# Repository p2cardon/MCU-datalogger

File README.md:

# MCU-datalogger
Example Kicad 6, Projects, Tips, and Recipes book
This repository has been created to learn basic functions of GIT usage, to synchronise KiCad projects
It's subject to be removed at any time without any warning
Don't rely on it's content

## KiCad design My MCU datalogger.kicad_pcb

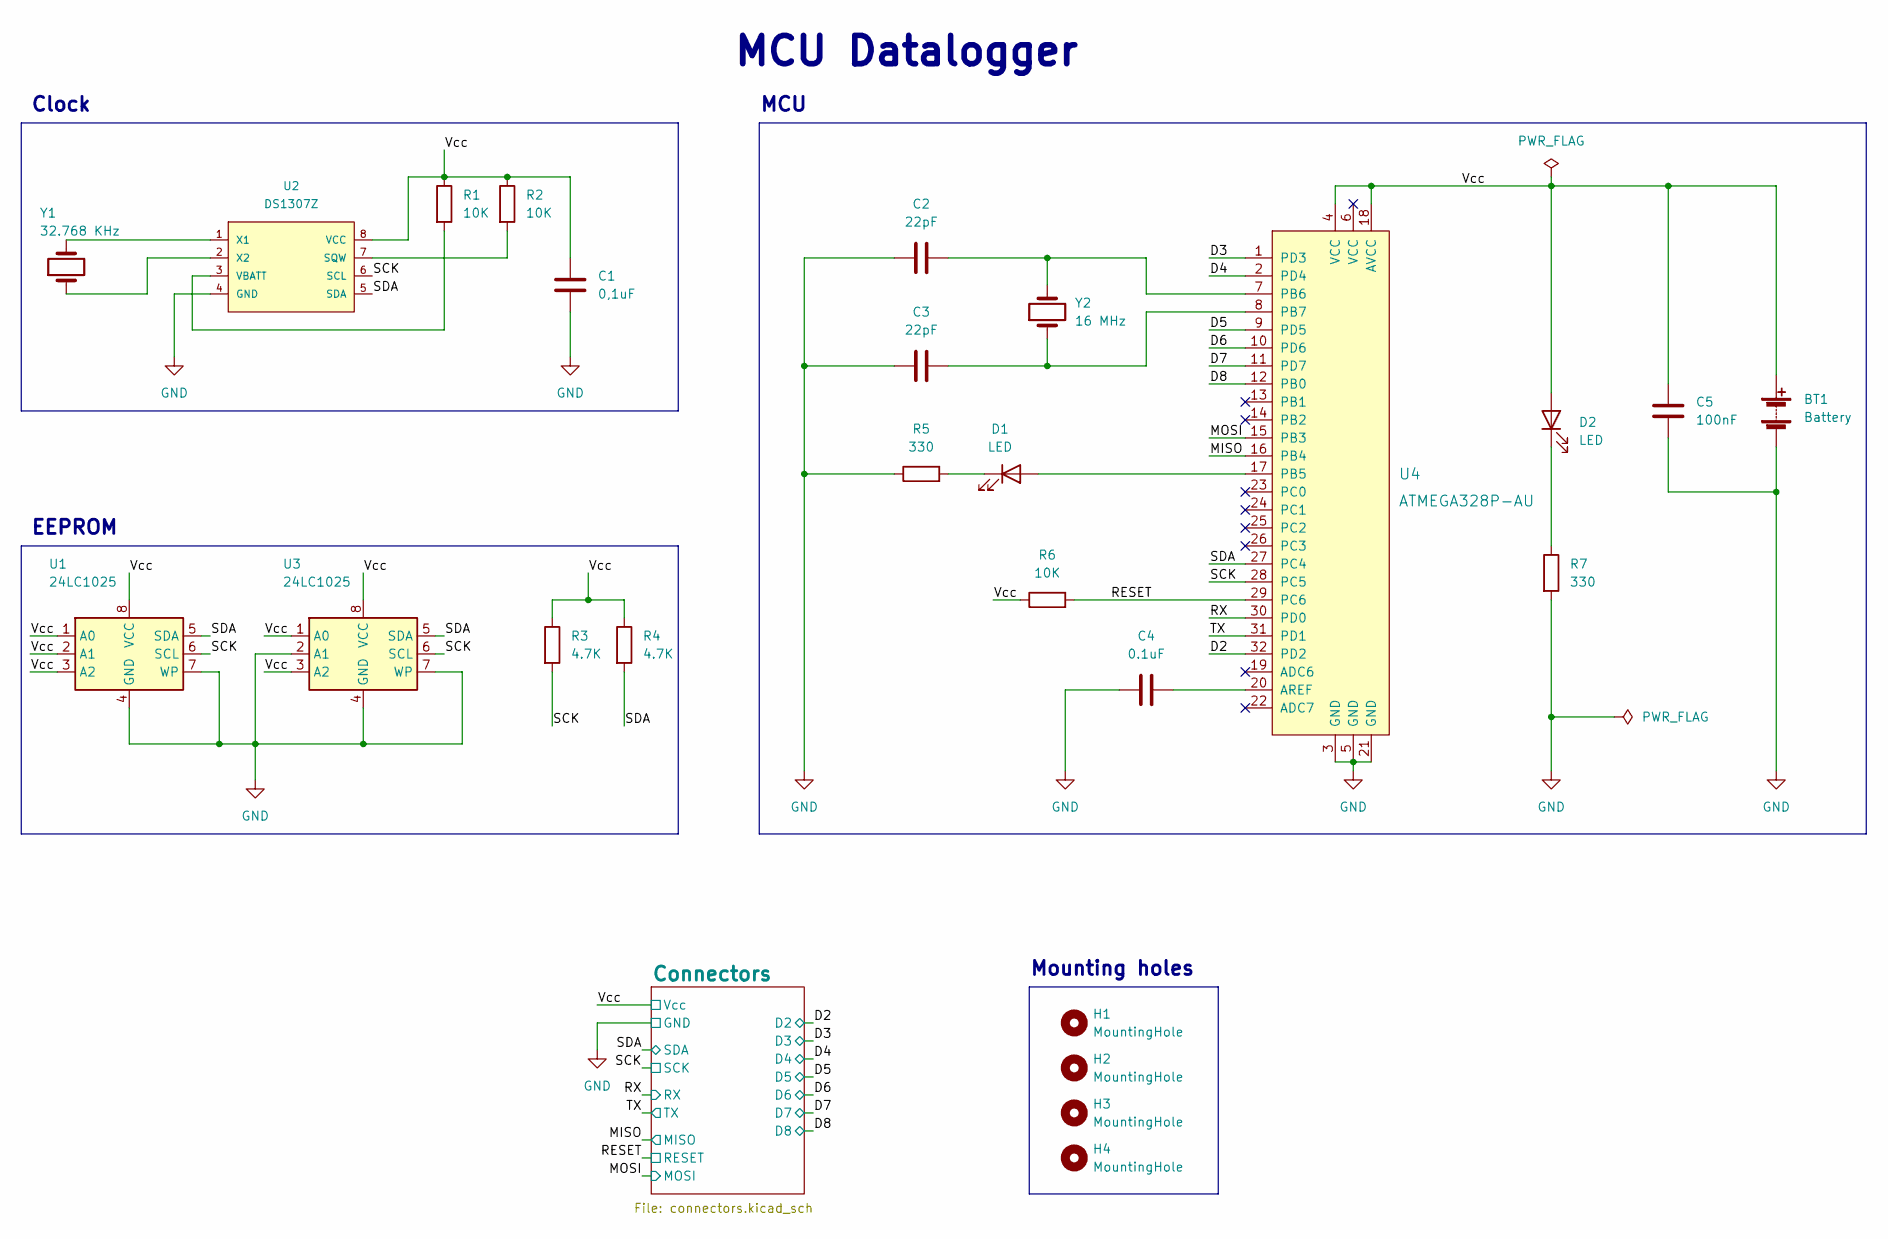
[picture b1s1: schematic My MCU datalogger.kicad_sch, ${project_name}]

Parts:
BT1: Battery; PinHeader_1x02_P2.54mm_Vertical
C1: 0,1uF; C_0805_2012Metric
C2, C3: 22pF; C_0805_2012Metric
C4: 0.1uF; C_0805_2012Metric
C5: 100nF; C_0805_2012Metric
D1, D2: LED; LED_0805_2012Metric
H1, H2, H3, H4: MountingHole; MountingHole_2.1mm
R1, R2, R6: 10K; R_0805_2012Metric
R3, R4: 4.7K; R_0805_2012Metric
R5, R7: 330; R_0805_2012Metric
U1, U3: 24LC1025; SOIC-8_3.9x4.9mm_P1.27mm
U2: DS1307Z; SO08-TIGHT
U4: ATMEGA328P-AU; TQFP-32_7x7mm; MPN ATMEGA328P-AU; Digi-Key_PN ATMEGA328P-AU-ND
Y1: 32.768 KHz; Crystal_SMD_5032-2Pin_5.0x3.2mm_HandSoldering
Y2: 16 MHz; Crystal_SMD_5032-2Pin_5.0x3.2mm_HandSoldering

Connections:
/D2: U4.32 (PD2); also elsewhere on the board
/D3: U4.1 (PD3); also elsewhere on the board
/D4: U4.2 (PD4); also elsewhere on the board
/D5: U4.9 (PD5); also elsewhere on the board
/D6: U4.10 (PD6); also elsewhere on the board
/D7: U4.11 (PD7); also elsewhere on the board
/D8: U4.12 (PB0); also elsewhere on the board
/MISO: U4.16 (PB4); also elsewhere on the board
/MOSI: U4.15 (PB3); also elsewhere on the board
/RESET: R6.2, U4.29 (PC6); also elsewhere on the board
/RX: U4.30 (PD0); also elsewhere on the board
/SCK: R3.2, U1.6 (SCL), U2.6 (SCL), U3.6 (SCL), U4.28 (PC5); also elsewhere on the board
/SDA: R4.2, U1.5 (SDA), U2.5 (SDA), U3.5 (SDA), U4.27 (PC4); also elsewhere on the board
/TX: U4.31 (PD1); also elsewhere on the board
/Vcc: BT1.1 (+), C1.1, C5.1, D2.2 (A), R1.1, R2.1, R3.1, R4.1, R6.1, U1.1 (A0), U1.2 (A1), U1.3 (A2), U1.8 (VCC), U2.8 (VCC), U3.1 (A0), U3.3 (A2), U3.8 (VCC), U4.4 (VCC), U4.18 (AVCC); also elsewhere on the board
GND: BT1.2 (-), C1.2, C2.1, C3.1, C4.1, C5.2, R5.1, R7.2, U1.4 (GND), U1.7 (WP), U2.4 (GND), U3.2 (A1), U3.4 (GND), U3.7 (WP), U4.3 (GND), U4.5 (GND), U4.21 (GND); also elsewhere on the board
unnamed: C2.2, U4.7 (PB6), Y2.2
unnamed: C3.2, U4.8 (PB7), Y2.1
unnamed: C4.2, U4.20 (AREF)
unnamed: D1.1 (K), R5.2
unnamed: D1.2 (A), U4.17 (PB5)
unnamed: D2.1 (K), R7.1
unnamed: R1.2, U2.3 (VBATT)
unnamed: R2.2, U2.7 (SQW)
unnamed: U2.1 (X1), Y1.2
unnamed: U2.2 (X2), Y1.1

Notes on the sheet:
EEPROM
MCU
MCU Datalogger
Clock
Mounting holes

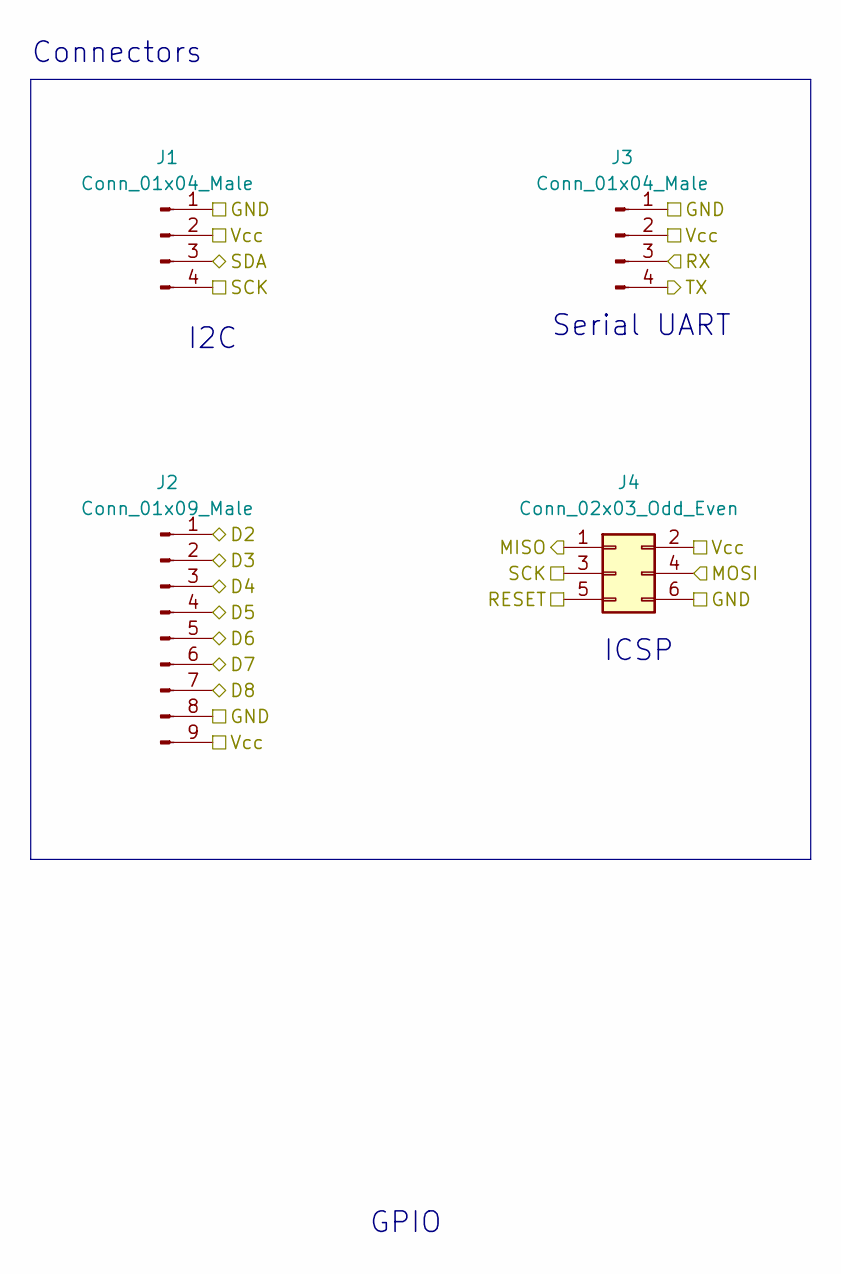
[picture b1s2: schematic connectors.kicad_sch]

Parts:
J1, J3: Conn_01x04_Male; PinHeader_1x04_P2.54mm_Vertical
J2: Conn_01x09_Male; PinHeader_1x09_P2.54mm_Vertical
J4: Conn_02x03_Odd_Even; PinHeader_2x03_P2.54mm_Vertical

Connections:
/D2: J2.1; also elsewhere on the board
/D3: J2.2; also elsewhere on the board
/D4: J2.3; also elsewhere on the board
/D5: J2.4; also elsewhere on the board
/D6: J2.5; also elsewhere on the board
/D7: J2.6; also elsewhere on the board
/D8: J2.7; also elsewhere on the board
/MISO: J4.1; also elsewhere on the board
/MOSI: J4.4; also elsewhere on the board
/RESET: J4.5; also elsewhere on the board
/RX: J3.3; also elsewhere on the board
/SCK: J1.4, J4.3; also elsewhere on the board
/SDA: J1.3; also elsewhere on the board
/TX: J3.4; also elsewhere on the board
/Vcc: J1.2, J2.9, J3.2, J4.2; also elsewhere on the board
GND: J1.1, J2.8, J3.1, J4.6; also elsewhere on the board

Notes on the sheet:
Connectors
I2C
Serial UART
GPIO
ICSP

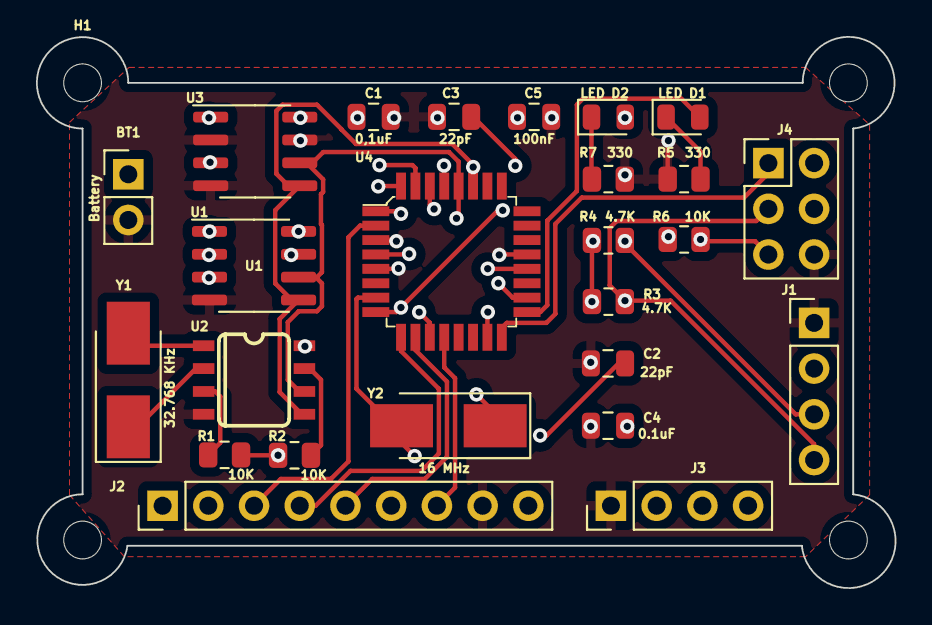
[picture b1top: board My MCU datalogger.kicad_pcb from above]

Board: 4 copper layers, 47.7 x 30.6 mm, 29 parts (0 on the bottom side), 26 nets.

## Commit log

2022-05-11 added resistor
2022-05-11 added capacitor
2022-05-11 testing with new capacitors
2022-05-11 Added annotation
2022-05-11 Update My MCU datalogger.kicad_sch
    Changed C5 to C25
2022-05-11 Added schematic title label
2022-05-11 Update My MCU datalogger.kicad_sch
    Fixed title
2022-05-11 Still working on title
2022-05-11 various changes
2022-05-11 build in progress
2022-05-11 added title
2022-05-11 work in progress
2022-05-12 Finalized schematics
2022-05-12 PCB Update
2022-05-12 Added missing footprints
2022-05-12 Fixed ERC errors in schematic
2022-05-12 Assigned Net classes
2022-05-12 Various fixes
2022-05-12 Various refinements
2022-05-13 Verification
2022-05-13 Layout 1 - Setup
2022-05-13 Initial layout
2022-05-13 Outline refinement
2022-05-13 Final outline
2022-05-13 Finalized
2022-05-14 Added front filled zone for Vcc net
2022-05-14 Routing improvements
2022-05-14 Generated Gerbers files
2022-05-14 4_layers final candidate
2022-05-14 Final version

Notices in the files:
My MCU datalogger.kicad_sch:
©2022 by P. CARDON
